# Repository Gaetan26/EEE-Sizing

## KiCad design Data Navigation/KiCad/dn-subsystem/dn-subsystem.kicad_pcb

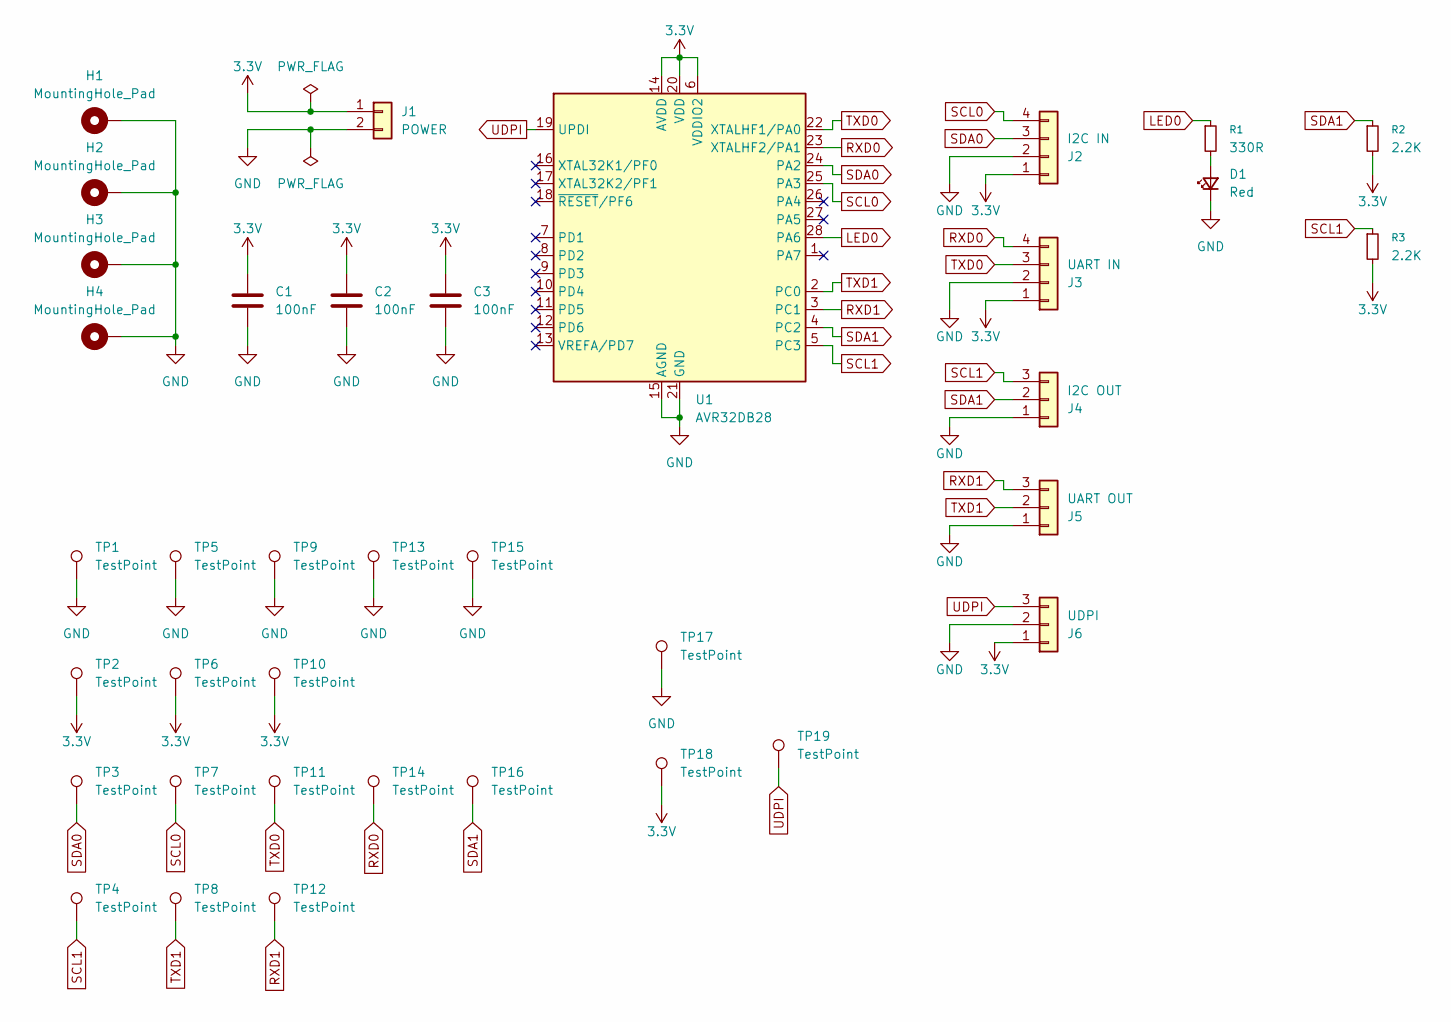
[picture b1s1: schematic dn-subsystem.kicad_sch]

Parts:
C1, C2, C3: 100nF; C_Disc_D5.0mm_W2.5mm_P5.00mm
D1: Red; LED_0805_2012Metric
H1, H2, H3, H4: MountingHole_Pad; MountingHole_3.5mm_Pad
J1: POWER; JST_XH_B2B-XH-A_1x02_P2.50mm_Vertical
J2: I2C IN; JST_XH_B4B-XH-A_1x04_P2.50mm_Vertical
J3: UART IN; JST_XH_B4B-XH-A_1x04_P2.50mm_Vertical
J4: I2C OUT; JST_XH_B3B-XH-A_1x03_P2.50mm_Vertical
J5: UART OUT; JST_XH_B3B-XH-A_1x03_P2.50mm_Vertical
J6: UDPI; JST_XH_B3B-XH-A_1x03_P2.50mm_Vertical
R1: 330R; R_0805_2012Metric
R2, R3: 2.2K; R_0805_2012Metric
TP1, TP2, TP3, TP4, TP5, TP6, TP7, TP8, TP9, TP10, TP11, TP12, TP13, TP14, TP15, TP16, TP17, TP18, TP19: TestPoint; TestPoint_Pad_D1.0mm
U1: AVR32DB28; DIP-28_W7.62mm

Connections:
3.3V: C1.1, C2.1, C3.1, J1.1, J2.1, J3.1, J6.1, R2.2, R3.2, TP2.1 (1_1), TP6.1 (1_1), TP10.1 (1_1), TP18.1 (1_1), U1.6 (VDDIO2), U1.14 (AVDD), U1.20 (VDD)
GND: C1.2, C2.2, C3.2, D1.1 (K), H1.1 (1_1), H2.1 (1_1), H3.1 (1_1), H4.1 (1_1), J1.2, J2.2, J3.2, J4.1, J5.1, J6.2, TP1.1 (1_1), TP5.1 (1_1), TP9.1 (1_1), TP13.1 (1_1), TP15.1 (1_1), TP17.1 (1_1), U1.15 (AGND), U1.21 (GND)
LED0: R1.1, U1.28 (PA6)
unnamed: D1.2 (A), R1.2
RXD0: J3.4, TP14.1 (1_1), U1.23 (XTALHF2/PA1)
RXD1: J5.3, TP12.1 (1_1), U1.3 (PC1)
SCL0: J2.4, TP7.1 (1_1), U1.25 (PA3)
SCL1: J4.3, R3.1, TP4.1 (1_1), U1.5 (PC3)
SDA0: J2.3, TP3.1 (1_1), U1.24 (PA2)
SDA1: J4.2, R2.1, TP16.1 (1_1), U1.4 (PC2)
TXD0: J3.3, TP11.1 (1_1), U1.22 (XTALHF1/PA0)
TXD1: J5.2, TP8.1 (1_1), U1.2 (PC0)
UDPI: J6.3, TP19.1 (1_1), U1.19 (UPDI)

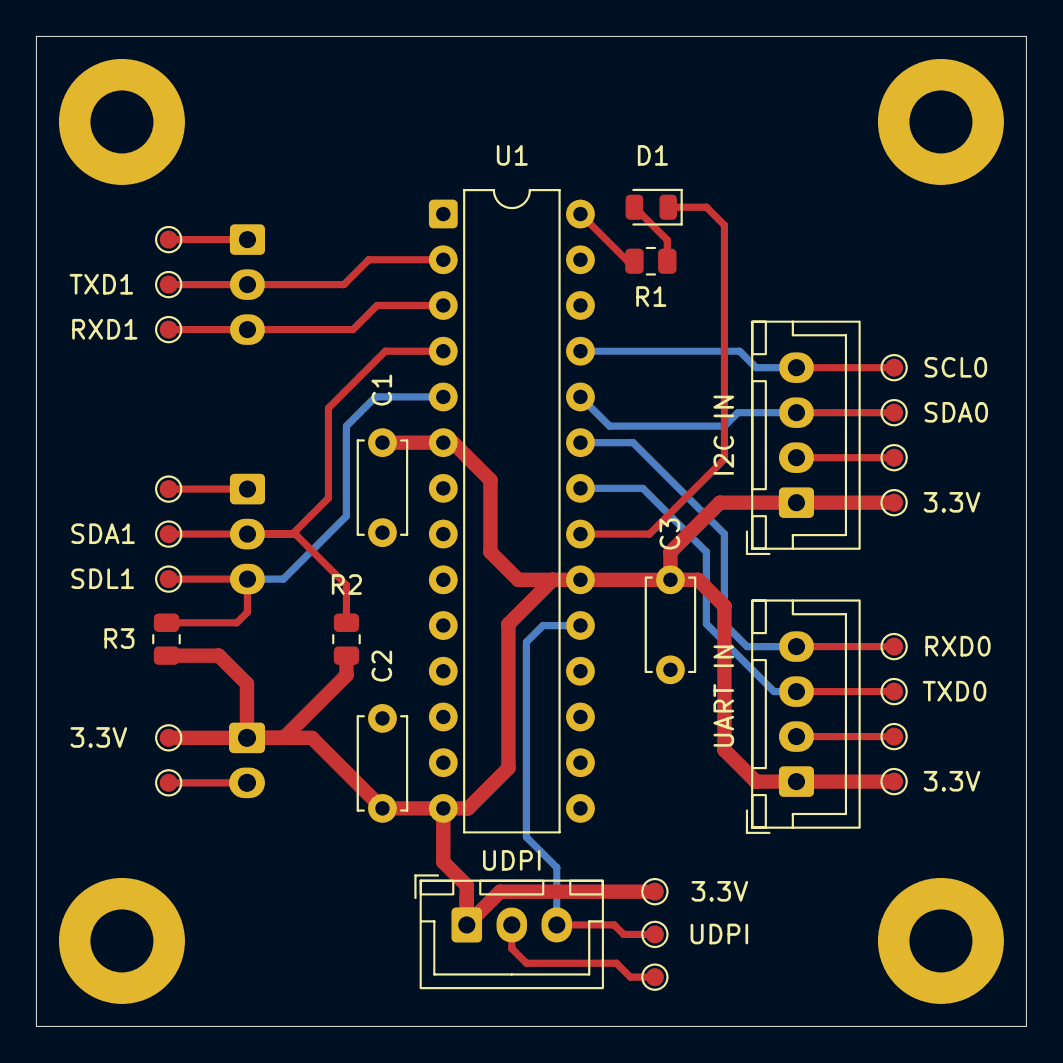
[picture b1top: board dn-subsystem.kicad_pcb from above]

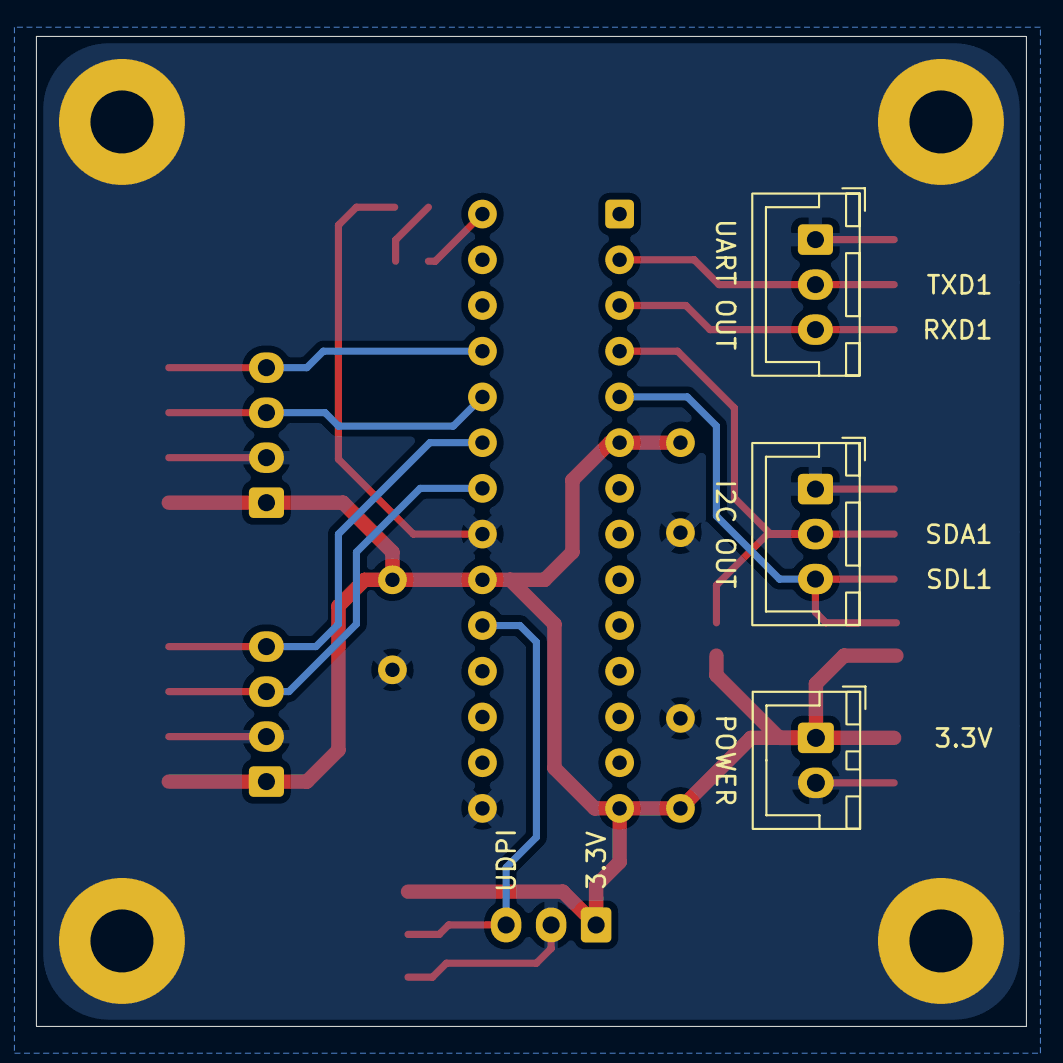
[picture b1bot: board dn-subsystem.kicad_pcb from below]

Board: 2 copper layers, 55.0 x 55.0 mm, 37 parts (3 on the bottom side), 13 nets.
